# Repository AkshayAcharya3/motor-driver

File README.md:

# PCB Design Project

## Overview
This is a custom PCB design featuring:

- **Microcontroller Circuit** with supporting components
- **LED Indicator (D1)** for output signaling
- **Resistor (R1)** for current limiting
- **Input/Output Connectors (J1, J2, J3, J4)** for easy interfacing
- **IC Components (U1 and main IC)** for circuit functionality

The board was designed to optimize **compactness**, **easy connectivity**, and **reliability**.

---

## Features
- Compact and clean PCB layout
- Properly labeled components
- Easy-to-solder through-hole and SMD parts
- Ready for prototyping and integration

## Components
| Reference | Component        | Description               |
|-----------|------------------|----------------------------|
| U1        | IC                | Supporting IC (e.g., driver) |
| Main IC   | Microcontroller/Driver IC | Central controller |
| R1        | Resistor          | Current limiter for LED    |
| D1        | LED               | Visual indicator           |
| J1-J3     | Terminal Blocks   | Power and signal connectors|
| J4        | Pin Header        | Signal/Programming header  |

---

## Author
**Akshay Acharya**  
*Electronics and Communication Engineering Student*

---

## License
This project is licensed under the [MIT License](LICENSE).

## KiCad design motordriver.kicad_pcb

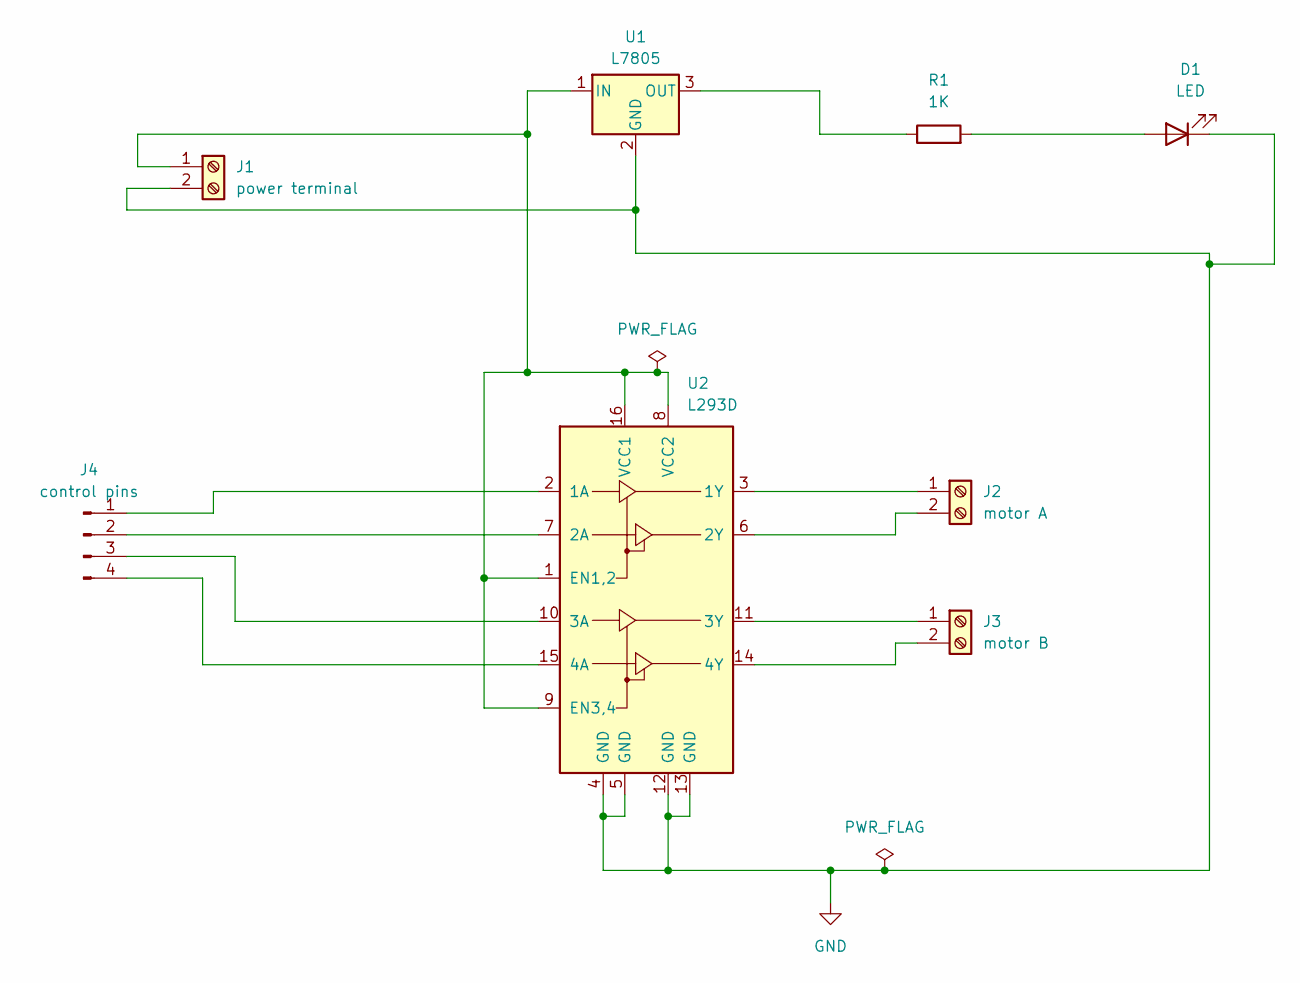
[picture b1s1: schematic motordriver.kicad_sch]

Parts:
D1: LED; LED_D3.0mm
J1: power terminal; TerminalBlock_Phoenix_MKDS-1,5-2-5.08_1x02_P5.08mm_Horizont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
J2: motor A; TerminalBlock_Phoenix_MKDS-1,5-2-5.08_1x02_P5.08mm_Horizont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
J3: motor B; TerminalBlock_Phoenix_MKDS-1,5-2-5.08_1x02_P5.08mm_Horizont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
J4: control pins; PinHeader_1x04_P1.00mm_Vertical
R1: 1K; R_Axial_DIN0309_L9.0mm_D3.2mm_P15.24mm_Horizontal
U1: L7805; Vishay_HVM-DIP-3_W7.62mm
U2: L293D; DIP-16_W7.62mm

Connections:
GND: D1.1 (K), J1.2, U1.2 (GND), U2.4 (GND), U2.5 (GND), U2.12 (GND), U2.13 (GND)
unnamed: D1.2 (A), R1.2
unnamed: J1.1, U1.1 (IN), U2.1 (EN1,2), U2.8 (VCC2), U2.9 (EN3,4), U2.16 (VCC1)
unnamed: J2.1, U2.3 (1Y)
unnamed: J2.2, U2.6 (2Y)
unnamed: J3.1, U2.11 (3Y)
unnamed: J3.2, U2.14 (4Y)
unnamed: J4.1, U2.2 (1A)
unnamed: J4.2, U2.7 (2A)
unnamed: J4.3, U2.10 (3A)
unnamed: J4.4, U2.15 (4A)
unnamed: R1.1, U1.3 (OUT)

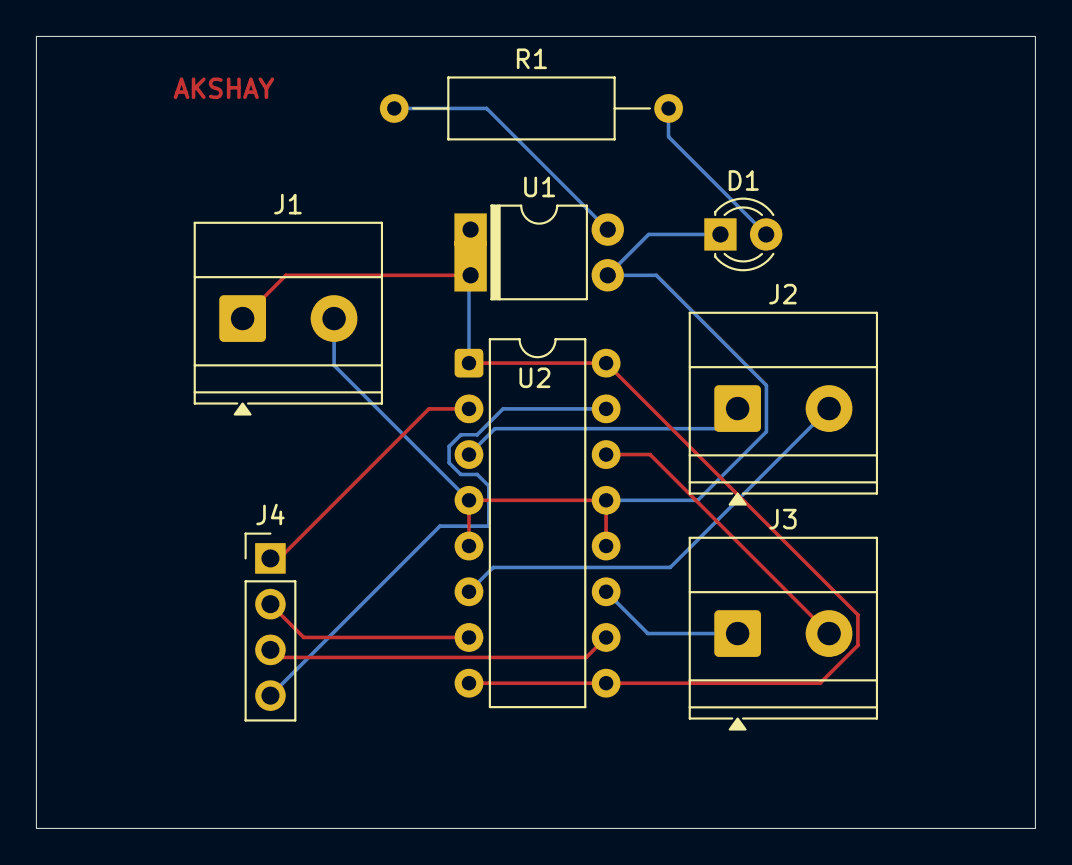
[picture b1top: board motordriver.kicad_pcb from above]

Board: 2 copper layers, 55.5 x 44.0 mm, 8 parts (0 on the bottom side), 12 nets.

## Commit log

2025-04-28 initial setup
2025-04-28 motor driver schematic
2025-04-28 footprints added
2025-04-28 pcb designed
2025-04-28 done
